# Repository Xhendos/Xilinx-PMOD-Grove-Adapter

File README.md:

# Xilinx-PMOD-Grove-Adapter

I wanted to try [Xilinx PYNQ Workshop](github.com/Xilinx/PYNQ_Workshop) in order to run HLS code on the FPGA fabric of the Zynq 7020 SoC. However, the workshop relies on [Grove](https://wiki.sipeed.com/soft/maixpy/en/modules/grove/index.html)-type sensors. 
There used to be a PMOD to Grove adapter board, but it is not for sale anymore ([original](https://pynq.readthedocs.io/en/v2.5.1/pynq_libraries/grove.html)). That is why I decided to make my own PMOD to Grove adapter board that has been tested and used for the PYNQ-Z2 board, but should work with other boards as well. 

# Bill of Material (BOM)

The most widely available option is AliExpress, that is where I ordered the components. The PCBs are ordered at JLCPCB.

Product  | Link
------------- | -------------
2x6 male pin header (angled) | [link](https://nl.aliexpress.com/item/1005007673111748.html?spm=a2g0o.order_list.order_list_main.31.56ed79d2fwsn0M&gatewayAdapt=glo2nld)
Grove connector  | [link](https://nl.aliexpress.com/item/32814974160.html?spm=a2g0o.order_list.order_list_main.25.56ed79d2fwsn0M&gatewayAdapt=glo2nld)

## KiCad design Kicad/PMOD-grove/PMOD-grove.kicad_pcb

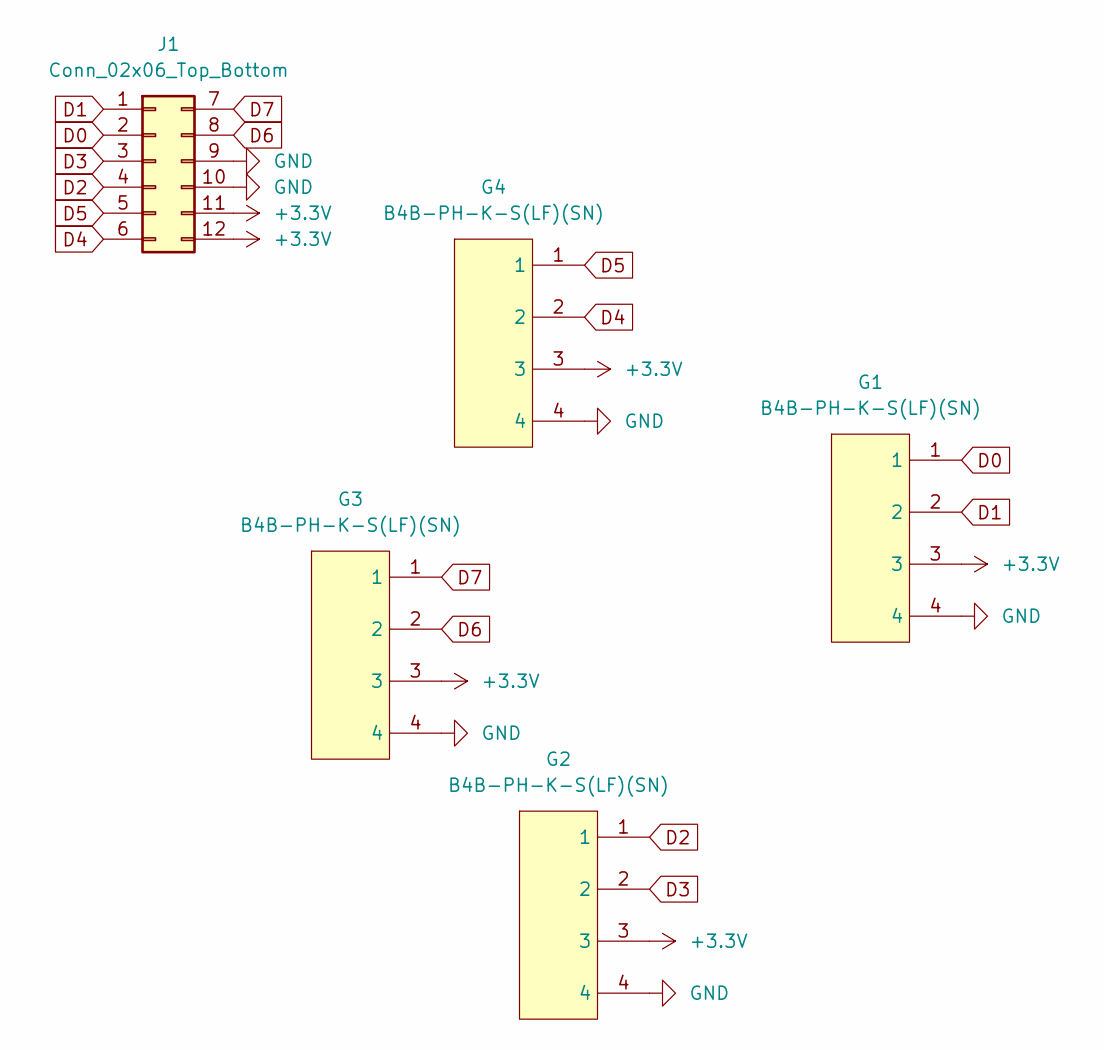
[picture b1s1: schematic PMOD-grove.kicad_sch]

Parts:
G1, G2, G3, G4: B4B-PH-K-S(LF)(SN); CONN-TH_B4B-PH-K-S; LCSC Part C131334
J1: Conn_02x06_Top_Bottom; PinHeader_2x06_P2.54mm_Vertical

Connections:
+3.3V: G1.3, G2.3, G3.3, G4.3, J1.11, J1.12
D0: G1.1, J1.2
D1: G1.2, J1.1
D2: G2.1, J1.4
D3: G2.2, J1.3
D4: G4.2, J1.6
D5: G4.1, J1.5
D6: G3.2, J1.8
D7: G3.1, J1.7
GND: G1.4, G2.4, G3.4, G4.4, J1.9, J1.10

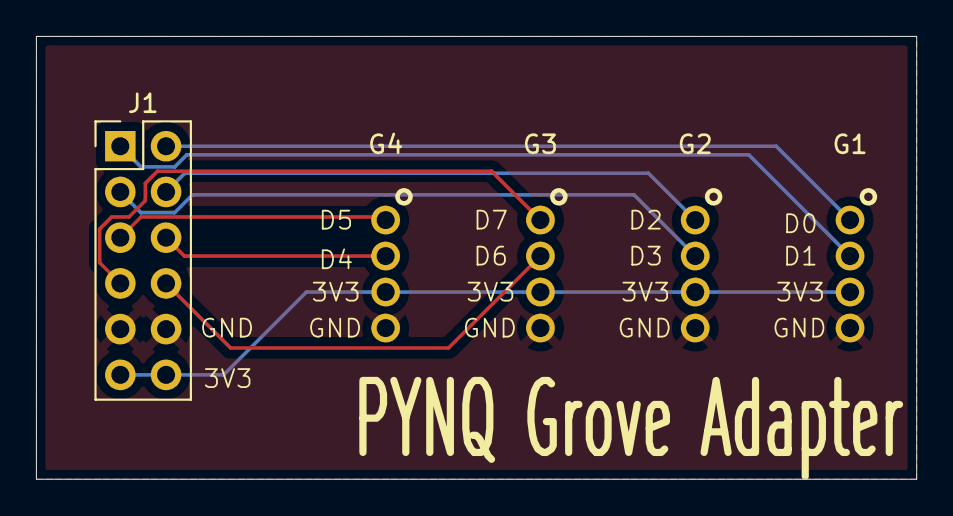
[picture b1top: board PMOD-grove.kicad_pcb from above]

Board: 2 copper layers, 48.9 x 24.6 mm, 5 parts (0 on the bottom side), 10 nets.

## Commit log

2025-11-07 Add KiCad project, Gerbers and Figures
2025-11-07 Updated README with some text and images
2025-11-07 Added Bill of Material section
2025-11-07 Added link to docs of PMOD to Grove adapter or the original one
